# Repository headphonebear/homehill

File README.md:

# 🏡 Homehill

**Homehill** is my homelab, kept as code: a small K3s cluster run strictly via
GitOps, plus a handful of standalone hosts running Docker Compose. Everything
here is declarative configuration — Kubernetes manifests, Helm values, Compose
files — applied to real machines at home. There is no application code to build;
"working" means the manifests are valid and the cluster agrees with Git.

Everything is internal-only: no port forwarding, services live under
`*.homehill.de` behind a local Pi-hole, with a Let's Encrypt wildcard certificate.

---

## 🗂️ What's in here

```
homehill/
├── clusters/        # 🍎 Orchard — the K3s cluster (the active focus)
│   ├── argocd/      #    one ArgoCD Application per app (+ the app-of-apps root)
│   ├── apps/        #    one local Helm umbrella chart per app
│   └── docs/        #    secrets workflow, troubleshooting, bootstrap
├── servers/         # Standalone hosts, Docker Compose, applied by hand
│   ├── barn/        #    🌾 workstation + Docker host
│   ├── belfry/      #    🔔 music server
│   ├── chick/       #    🐣 development server
│   └── dovecote/    #    🕊️ Pi-hole DNS
├── devices/         # 🛰️ Station to Station — self-built ESP32 sensor stations
│   └── station-beardesk/  # firmware (ESPHome), wiring, PCB, enclosure
├── docs/            # Repo-wide: UID/GID schema for users and services
├── CHANGELOG.md     # What changed, and why
└── CLAUDE.md        # Working conventions for AI-assisted sessions
```

---

## 🍎 Orchard — the cluster

Three nodes on **Alpine Linux** running **K3s**: `apple` (control plane),
`lemon` and `plum`.

**How it's run.** Git is the source of truth. An ArgoCD *app-of-apps* watches
[`clusters/argocd/orchard/`](clusters/argocd/orchard/) and deploys every
`Application` it finds there. Each app is a small umbrella chart under
[`clusters/apps/`](clusters/apps/) that pins the upstream chart and carries the
repo-specific extras (IngressRoutes, SealedSecrets, middlewares). Changes are
made by committing — not by `kubectl apply`. Stateful apps sync manually on
purpose.

**Platform**

| Concern | Tool |
|---|---|
| GitOps | ArgoCD (manages itself) |
| Ingress | Traefik |
| TLS | cert-manager + Hetzner DNS-01 → wildcard `*.homehill.de` |
| Storage | Longhorn, 3 replicas across all nodes |
| Databases | CloudNativePG, with WAL archiving + backups to S3 |
| Secrets | Sealed Secrets — only encrypted secrets ever touch Git |
| Monitoring | kube-prometheus-stack + VictoriaMetrics |

**Apps:** Forgejo (`git.homehill.de`), Vaultwarden, memos, Isley, Qdrant —
plus HTTPS front doors for the Pi-hole admin UI and the music server.

Start here: [`clusters/README.md`](clusters/README.md) ·
secrets: [`clusters/docs/SECRETS.md`](clusters/docs/SECRETS.md) ·
when things break: [`clusters/docs/TROUBLESHOOTING.md`](clusters/docs/TROUBLESHOOTING.md)

---

## 🖥️ Standalone hosts

| Host | Role | Details |
|---|---|---|
| 🌾 **barn** | Workstation and Docker host; GPU playground | [`servers/barn/`](servers/barn/) |
| 🔔 **belfry** | Music server (Lyrion Music Server), gapless, tag-respecting | [`servers/belfry/`](servers/belfry/) |
| 🐣 **chick** | Development server (PostgreSQL, Valkey) | [`servers/chick/`](servers/chick/) |
| 🕊️ **dovecote** | Pi-hole — DNS for the whole house, independent of the cluster | [`servers/dovecote/`](servers/dovecote/) |

---

## 🛰️ Station to Station — self-built devices

Small ESP32 stations that measure the air in the house — CO₂, temperature,
humidity, light — with no cloud and no hub. Everything for a station lives in
one folder: ESPHome firmware, wiring, the KiCad carrier board and the printable
enclosure. One station per place, one database for all of them.

| Station | Place | Details |
|---|---|---|
| 🐻 **Beardesk** | Stefan's desk, home office | [`devices/station-beardesk/`](devices/station-beardesk/) |

Start here: [`devices/README.md`](devices/README.md)

---

## 🤝 Built with

Homehill is designed, built and run by me — **Stefan**
([Headphonebear](https://github.com/headphonebear)) 🐻.

Since 2026 I build it together with **Claude** (Anthropic) as my AI pair
engineer: drafts, research, manifests and documentation. I review every change
and push it myself. I'm not going to pretend I built this alone — the reasoning
lives in the commit messages and the `# WHY:` comments, written by both of us.

---

## 🎧 Inspired by

- **Massive Attack, Portishead, Kate Bush** — the soundtrack
- **Radiohead** — *Planet Telex* and *No Surprises* belong on every SRE playlist
- **Terry Pratchett, Philip K. Dick, The Simpsons** — the worldview
  (the AI here is Blade Runner, not Terminator)
- **Alpine Linux, Kubernetes and the self-hosting community** — the foundation

---

## 📝 A note on reuse

This is personal infrastructure, shared for inspiration. Hostnames, IPs and
choices are specific to my home. Take the ideas, not the configs — and build
*your* homelab, not mine.

---

*Last updated: 2026-10-10*

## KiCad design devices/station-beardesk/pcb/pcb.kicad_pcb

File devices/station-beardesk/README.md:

# 🛰️ Station Beardesk

The first station of **Station to Station** (built as "Station 1" on
2026-11-21). Lives on the Honeycomb Storage Wall behind Stefan's monitor —
the home office.

## What it does

- **Measures** CO₂, temperature and humidity (Sensirion SCD41) and ambient
  light (TSL2591)
- **Air traffic light** on an RGB LED: green ≤ 800 ppm → red ≥ 1400 ppm,
  pulses from 1600 ppm, blinks blue when humidity is above 65 %
- **Dims itself** to the room light — bright in daylight, a faint glow at night
- **OLED only on demand**: press the button, the values show for 30 s.
  Nobody (no bear) stares at a display all day

## Hardware

ESP32-DevKit HW-394 (WROOM-32D, USB-C) · SCD41 · TSL2591 · SSD1306 OLED
0.96″ 128×64 · RGB LED (common cathode, 3 × 220 Ω) · push button.
All sensors on one I²C bus at 400 kHz. Wiring pin by pin: [`PINOUT.md`](PINOUT.md).

## Status

| Step | State |
|---|---|
| Breadboard build, ESPHome config | ✅ 2026-11-21, running daily since |
| Carrier PCB (KiCad, `pcb/`) | 🛠️ in design |
| Enclosure (`enclosure/`, by tinkerbear) | 🛠️ waits for PCB dimensions |
| WiFi + values to Orchard (VictoriaMetrics) | ⏳ |

⚠️ The board on the wall still runs the old firmware named `station1`.
It only becomes `station-beardesk` on the next flash.

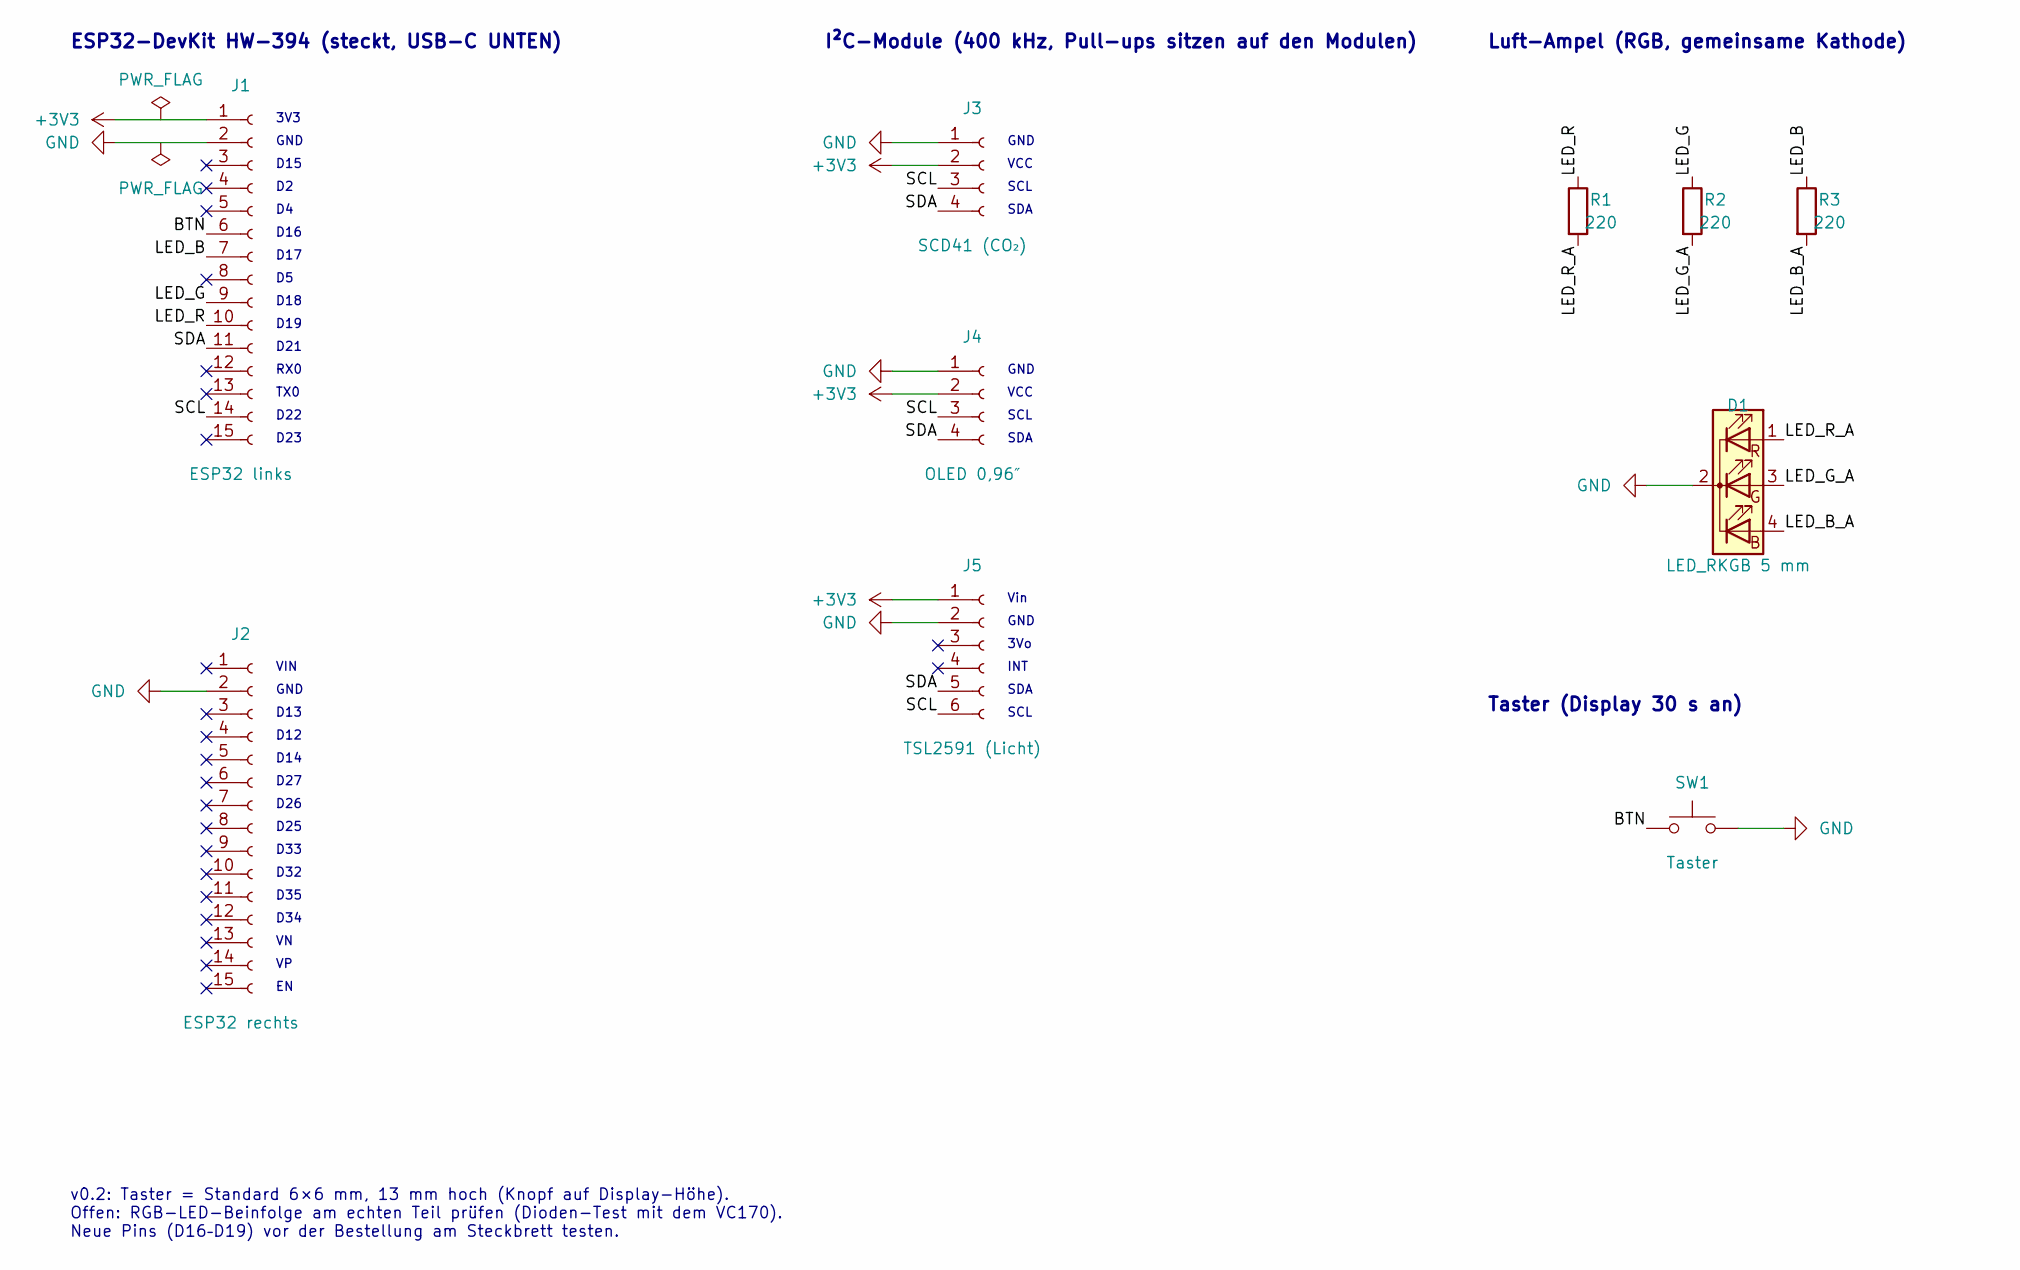
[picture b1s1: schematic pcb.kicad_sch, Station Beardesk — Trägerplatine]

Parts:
D1: LED_RKGB 5 mm; LED_D5.0mm-4_RGB_Staggered_Pins
J1: ESP32 links; PinSocket_1x15_P2.54mm_Vertical
J2: ESP32 rechts; PinSocket_1x15_P2.54mm_Vertical
J3: SCD41 (CO₂); PinSocket_1x04_P2.54mm_Vertical
J4: OLED 0,96″; PinSocket_1x04_P2.54mm_Vertical
J5: TSL2591 (Licht); PinSocket_1x06_P2.54mm_Vertical
R1, R2, R3: 220; R_Axial_DIN0207_L6.3mm_D2.5mm_P7.62mm_Horizontal
SW1: Taster; SW_PUSH_6mm_H13mm

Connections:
+3V3: J1.1, J3.2, J4.2, J5.1
/BTN: J1.6, SW1.1
/LED_B: J1.7, R3.1
/LED_B_A: D1.4 (BA), R3.2
/LED_G: J1.9, R2.1
/LED_G_A: D1.3 (GA), R2.2
/LED_R: J1.10, R1.1
/LED_R_A: D1.1 (RA), R1.2
/SCL: J1.14, J3.3, J4.3, J5.6
/SDA: J1.11, J3.4, J4.4, J5.5
GND: D1.2 (K), J1.2, J2.2, J3.1, J4.1, J5.2, SW1.2

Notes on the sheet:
ESP32-DevKit HW-394 (steckt, USB-C UNTEN)
3V3
GND
D15
D16
D17
D18
D19
D21
RX0
TX0
D22
D23
VIN
D13
D12
D14
D27
D26
D25
D33
D32
D35
D34
I²C-Module (400 kHz, Pull-ups sitzen auf den Modulen)
VCC
SCL
SDA
Vin
3Vo
INT
Luft-Ampel (RGB, gemeinsame Kathode)
Taster (Display 30 s an)
v0.2: Taster = Standard 6×6 mm, 13 mm hoch (Knopf auf Display-Höhe). Offen: RGB-LED-Beinfolge am echten Teil prüfen (Dioden-Test mit dem VC170). Neue Pins (D16–D19) vor der Bestellung am Steckbrett testen.

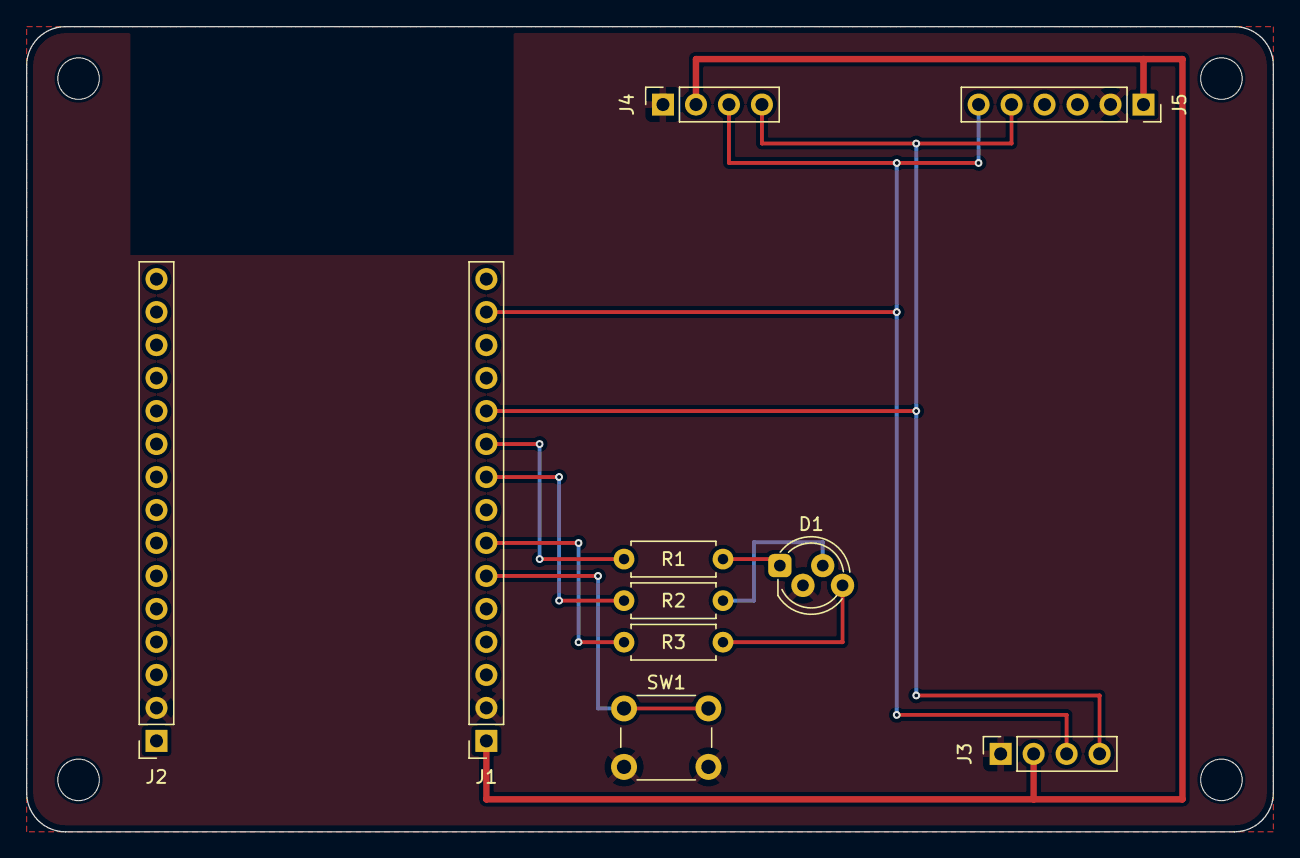
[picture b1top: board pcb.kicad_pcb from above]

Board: 2 copper layers, 96.0 x 62.0 mm, 14 parts (0 on the bottom side), 11 nets.

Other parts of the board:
H1, H2, H3, H4: M3; MountingHole_3.2mm_M3

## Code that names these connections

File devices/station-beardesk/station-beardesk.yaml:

# ╔══════════════════════════════════════════════════════════════╗
# ║  Station Beardesk 🛰️ — Raumklima am Schreibtisch des Bären    ║
# ║  Projekt „Station to Station“, Knoten Nr. 1 (ex „Station 1“)  ║
# ║  ESP32-DevKit HW-394 + Sensirion SCD41 (CO₂/Temp/Feuchte)     ║
# ║  Gebaut 2026-11-21 von Stefan (Hände) + coder (Konfig)        ║
# ╚══════════════════════════════════════════════════════════════╝
#
# WHY ohne WLAN: Erster Test nur über USB/Seriell. Keine Zugangsdaten
#   nötig, nichts verlässt den Schreibtisch. WLAN + Export zu Orchard
#   kommen in Schritt 2 (dann mit secrets.yaml, nie im Klartext hier).

esphome:
  name: station-beardesk
  friendly_name: "Station Beardesk"
  # WHY: Nach dem Start zeigt das Display 30 s lang die Werte, dann geht es aus.
  on_boot:
    priority: -100
    then:
      - script.execute: screen_timeout

esp32:
  board: esp32dev

# Ausgabe über USB-Seriell (115200 Baud). Hier lesen wir die Werte ab.
logger:
  level: DEBUG  # WHY DEBUG: erst hier loggt ESPHome die Messwerte (INFO verschluckt sie)

# I²C-Bus: Standard-Pins des ESP32.
#   SDA = D21 (grünes Kabel), SCL = D22 (oranges Kabel)
# WHY scan: Beim Start listet der ESP32 alle gefundenen Adressen.
#   Der SCD41 sollte als 0x62 auftauchen. Taucht nichts auf → Verkabelung.
i2c:
  sda: GPIO21
  scl: GPIO22
  scan: true
  # WHY 400 kHz: Mit dem Standard (50 kHz) brauchte jedes Display-Update ~220 ms
  #   und blockierte die Hauptschleife → Tasterdrücke gingen verloren.
  #   Alle drei Geräte (SCD41, SSD1306, TSL2591) können 400 kHz.
  frequency: 400kHz

sensor:
  # Lichtsensor fürs Auto-Dimmen der Luft-Ampel (I²C 0x29, gleicher Bus)
  - platform: tsl2591
    address: 0x29
    update_interval: 5s
    gain: auto
    calculated_lux:
      name: "Helligkeit"
      id: lux
      on_value:
        - logger.log:
            format: "💡 Licht: %.1f lx"
            args: [x]
            level: INFO

  - platform: scd4x
    co2:
      name: "CO2"
      id: co2
      # WHY on_value: ESPHome 2026.11 zeigt die Messwerte im Log nicht von allein
      #   an (nur "Warning flag cleared"). So stehen sie garantiert da.
      on_value:
        - logger.log:
            format: "🛰️ CO2: %.0f ppm"
            args: [x]
            level: INFO
    temperature:
      name: "Temperatur"
      id: temp
      on_value:
        - logger.log:
            format: "🌡️ Temperatur: %.1f °C"
            args: [x]
            level: INFO
    humidity:
      name: "Luftfeuchte"
      id: hum
      on_value:
        - logger.log:
            format: "💧 Luftfeuchte: %.1f %%"
            args: [x]
            level: INFO
    # WHY 10 s: zum Zuschauen beim ersten Test. Später 60 s reicht für Raumklima.
    update_interval: 10s

# ── Display ──────────────────────────────────────────────────────
# 0,96″ OLED, 128×64, SSD1306, I²C 0x3C (auf der Platine „0x78“ = 8-Bit-Schreibweise).
# Hängt am selben Bus wie der SCD41 (0x62) → keine Kollision.
# WHY gfonts: ESPHome braucht Schriftdateien; Roboto wird beim Kompilieren geholt.
font:
  - file: "gfonts://Roboto"
    id: f_big
    size: 26
  - file: "gfonts://Roboto"
    id: f_small
    size: 12

display:
  - platform: ssd1306_i2c
    id: oled
    model: "SSD1306 128x64"
    address: 0x3C
    update_interval: 2s
    lambda: |-
      it.print(0, 0, id(f_small), "Beardesk");
      if (id(co2).has_state()) {
        it.printf(0, 14, id(f_big), "%.0f ppm", id(co2).state);
      } else {
        it.print(0, 14, id(f_big), "...");
      }
      if (id(temp).has_state() && id(hum).has_state()) {
        it.printf(0, 48, id(f_small), "%.1f C   %.0f %%", id(temp).state, id(hum).state);
      }

# ── Luft-Ampel: RGB-LED (gemeinsame Kathode, langes Bein an Minus) ──
# v0.2 (Platine): D19 = Rot, D18 = Grün, D17 = Blau  (Steckbrett bis 2026-11-23: D27/D26/D25)
# WHY umgezogen: Auf der Platine steht der ESP32 auf dem Kopf (USB-C unten). Die rechte
#   Pinreihe zeigt dann zum Display – LED + Taster gehören auf diese Seite.
#   D2/D5/D12/D15 bewusst NICHT: Strapping-Pins, die der ESP32 beim Booten ausliest.
# ⚠️ Vor dem nächsten Flashen das Steckbrett entsprechend umstecken (Test vor der Bestellung).
# WHY LED statt Display: Ein Licht nimmt man nebenbei wahr, ein Bildschirm
#   fordert Aufmerksamkeit. Ruhige Technik für ADHS-/Autismus-Köpfe.
output:
  - { platform: ledc, pin: GPIO19, id: led_r }
  - { platform: ledc, pin: GPIO18, id: led_g }
  - { platform: ledc, pin: GPIO17, id: led_b }

light:
  - platform: rgb
    id: air_led
    name: "Luft-Ampel"
    red: led_r
    green: led_g
    blue: led_b
    restore_mode: ALWAYS_OFF
    # WHY 1.0: ESPHome rechnet sonst Gamma 2,8 drauf. Unsere Lux-Kurve ist
    #   schon an das Auge angepasst; doppelt gerechnet wird alles winzig dunkel
    #   und die Unterschiede verschwinden.
    gamma_correct: 1.0

# Farblogik (alle 2 s):
#   CO₂ ≤ 800 ppm grün → ~1100 gelb → ≥ 1400 rot (fließend)
#   CO₂ ≥ 1600 ppm: langsames Pulsieren (hell/dunkel im Wechsel)
#   Luftfeuchte > 65 %: im Wechsel blau dazwischen (Schimmel-Warnung)
# Helligkeit folgt dem Raumlicht (TSL2591): nachts gedimmt, tags heller.
interval:
  - interval: 2s
    then:
      - lambda: |-
          static uint32_t tick = 0;
          tick++;
          if (!id(co2).has_state()) return;
          float c = id(co2).state;
          float t = (c - 800.0f) / 600.0f;
          if (t < 0) t = 0;
          if (t > 1) t = 1;
          float r = t < 0.5f ? 2.0f * t : 1.0f;
          float g = t < 0.5f ? 1.0f : 2.0f * (1.0f - t);
          float b = 0.0f;
          // WHY log-Skala: Das Auge empfindet Helligkeit logarithmisch.
          //   ~1 lx (Nacht) → 0,04 · 10 lx → 0,16 · 100 lx → 0,27 · ≥1000 lx → 0,5
          //   Ohne Lichtwert: feste 0,35 wie bisher.
          float bright = 0.35f;
          if (id(lux).has_state() && !std::isnan(id(lux).state)) {
            float l = id(lux).state;
            if (l < 1.0f) l = 1.0f;
            bright = 0.04f + 0.115f * log10f(l);
            if (bright > 0.5f) bright = 0.5f;
          }
          bool humid = id(hum).has_state() && id(hum).state > 65.0f;
          if (humid && (tick % 2 == 0)) { r = 0; g = 0; b = 1; }
          if (c >= 1600.0f && (tick % 2 == 1)) bright *= 0.2f;
          ESP_LOGI("ampel", "🚦 R%.2f G%.2f B%.2f · Helligkeit %.2f", r, g, b, bright);
          auto call = id(air_led).turn_on();
          call.set_rgb(r, g, b);
          call.set_brightness(bright);
          // WHY 0 (Test 2026-11-21): Mit Überblendung blieb die LED sichtbar
          //   unverändert, obwohl die Werte stimmten. Erst direkt setzen und prüfen.
          call.set_transition_length(0);
          call.perform();

# ── Taster: Display auf Abruf ────────────────────────────────────
# Taster zwischen D16 (v0.2, Steckbrett bis 2026-11-23: D33) und GND. Interner Pull-up,
# deshalb „inverted“: gedrückt = Verbindung zu GND = an.
binary_sensor:
  - platform: gpio
    name: "Taster"
    pin:
      number: GPIO16
      mode: INPUT_PULLUP
      inverted: true
    # WHY kein Interrupt (Test 2026-11-21): Im Interrupt-Modus kamen Tastendrücke
    #   erst ~5 s später an, gebündelt direkt nach jeder TSL2591-Messung.
    #   Abfragen in der Schleife (polling) umgeht das.
    use_interrupt: false
    filters:
      - delayed_on: 30ms   # WHY: Prellen des mechanischen Kontakts schlucken
    on_press:
      - logger.log: { format: "👆 Taster gedrückt → Display an", level: INFO }
      - script.execute: screen_timeout

script:
  - id: screen_timeout
    mode: restart   # WHY: erneutes Drücken verlängert die 30 s
    then:
      - lambda: id(oled).turn_on();
      - delay: 30s
      - lambda: id(oled).turn_off();
